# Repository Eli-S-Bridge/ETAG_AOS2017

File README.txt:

ETAG RFID reader Version1
(Distrubted at the American Ornithological Society Meeting, Lansing, MI, August 2017.

This repository contains:
  1) Eagle design files for the circuit board
  2) A board reference for using the Arduino app with the circuit board.
  3) Arduino code to install on the circuit board

SOFTWARE:

See the setup manual.

HARDWARE:

You can power the board from your USB port or use a 5V battery. 6V batteries seem to work OK too. We’ve tested 4AA batteries in series (which give ~6V). You can power the reader from the USB port or the push-in connectors. Check the + and - labels on the board before connecting the battery leads. The large switch on the circuit board alternates between power sources. If you have both USB and a battery connected, you will not really be able to turn the device off (but you can always use the reset button).

Antenna coils should have inductance of approximately 1.3 milliHenries. You can make the coils yourself by wrapping magnet wire around a form and measuring the inductance until you get it right. Don’t make them bigger than 15cm in diameter or they won’t work very well. You can also buy 1.25mH antennas that work pretty well here:

https://store.qkits.com/rfid/125khz-antenna-for-rfid-controllers-51-5mm.html

Tags need to work at 125kHz and follow the EM4100 communication protocol. Biomark tags generally follow the ISO11784/5 communication protocol will not work. Our favorite tag suppliers are www.cyntag.com (for PITtag style tags) and ibtechnology.co.uk (for RFID leg bands - look for “avian products”)

OTHER RESOURCES:

YouTube video demonstration: https://www.youtube.com/watch?v=-Nv7rSirzx8

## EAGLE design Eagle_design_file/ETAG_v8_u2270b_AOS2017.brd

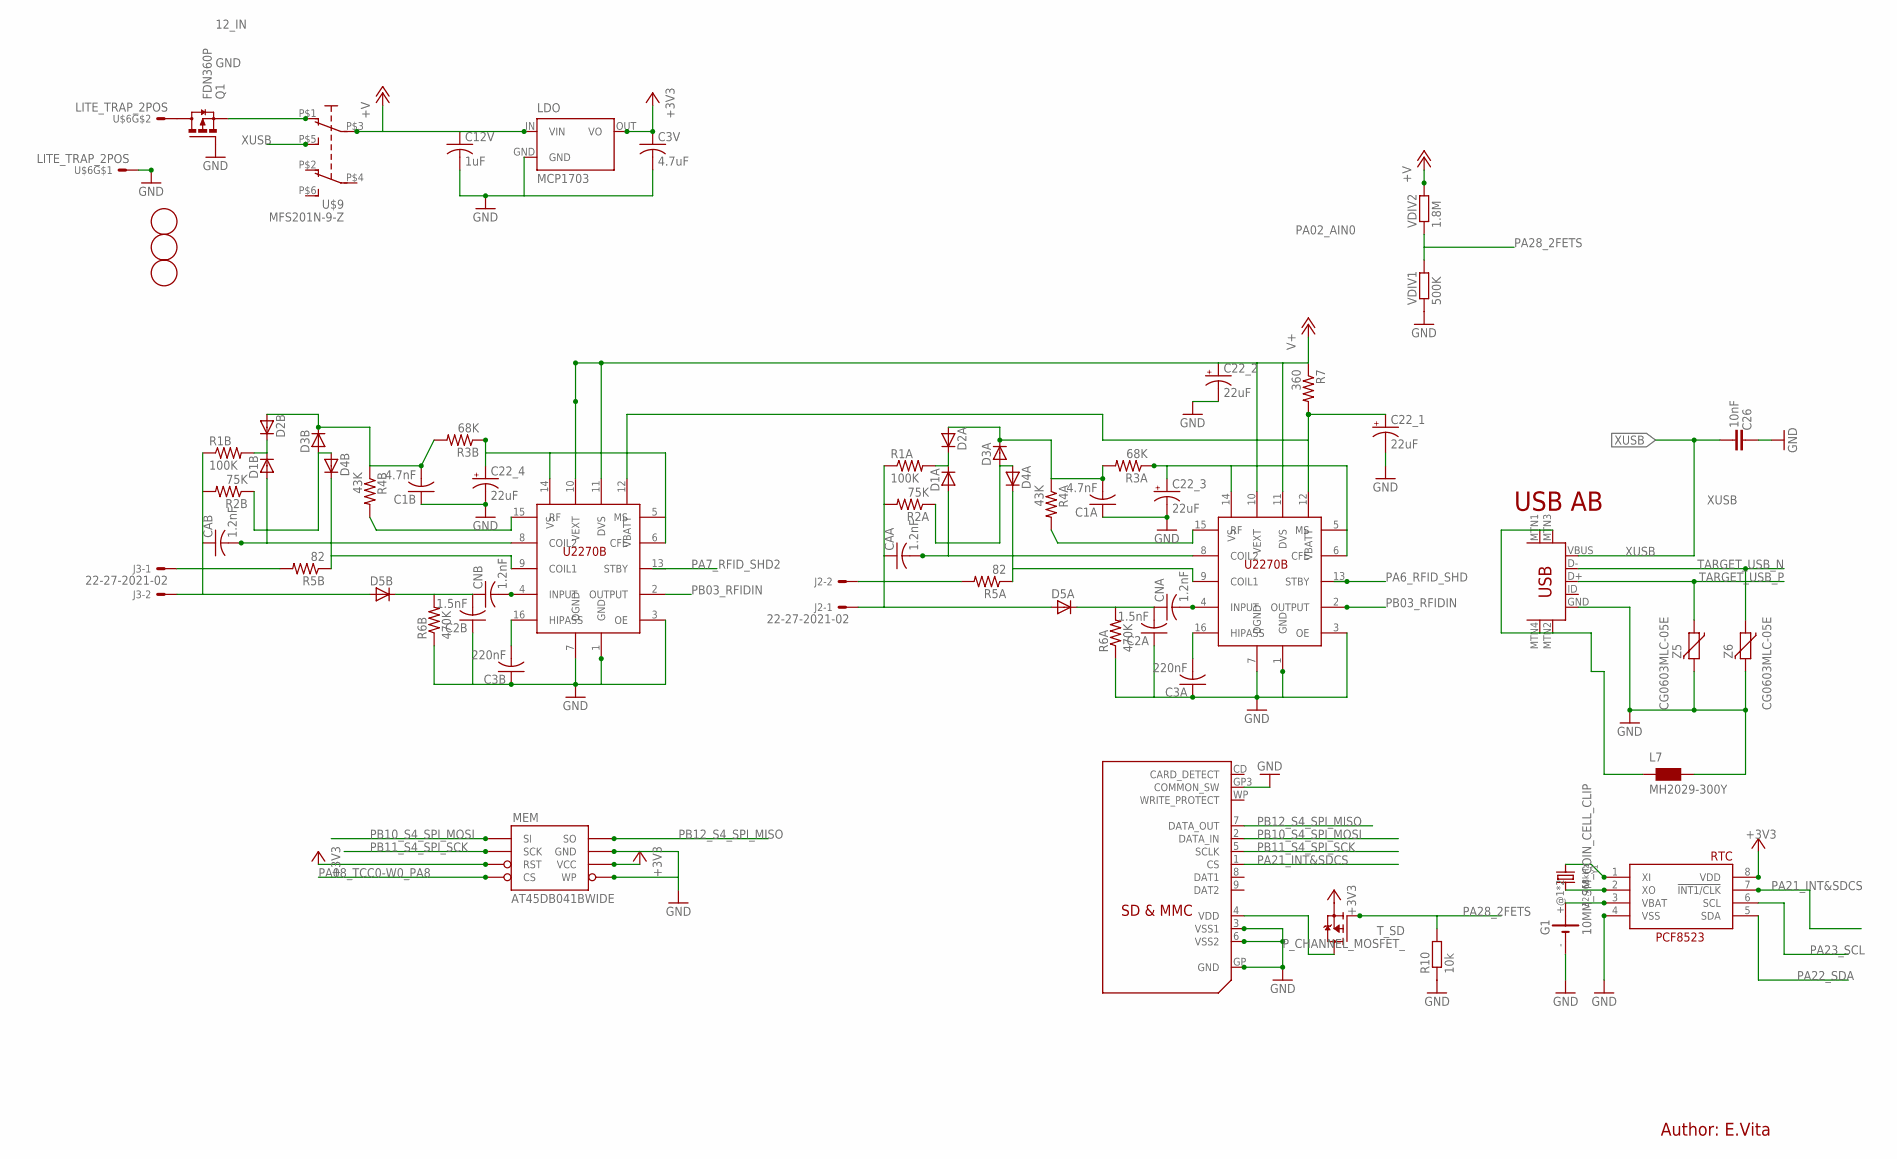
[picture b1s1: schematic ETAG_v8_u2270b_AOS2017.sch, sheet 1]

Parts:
C1A, C1B: 4.7nF; C0603-ROUND
C2A, C2B: 1.5nF; C0805
C3A, C3B: 220nF; C0603-ROUND
C3V: 4.7uF; C0805
C12V: 1uF; C0805
C22_1, C22_2, C22_3, C22_4: 22uF; 153CLV-0505
C26: 10nF; C0603-ROUND
CAA: 1.2nF; C0805
CAB: 1.2nF; C0805
CNA: 1.2nF; C0805
CNB: 1.2nF; C0805
D1A, D1B, D2A, D2B, D3A, D3B, D4A, D4B, D5A, D5B: D-GLASS_MELF; SOT-23_2PAD
FD1, FD2, FD3: FIDUCIALMOUNT; FIDUCIA-MOUNT
G1: 10MM_SM_COIN_CELL_CLIP
J2, J3: 22-27-2021-02; 6410-02
L7: MH2029-300Y; 0805
LDO: MCP1703; SOT89
MEM: AT45DB041BWIDE; SO08WIDE
Q1: FDN360P; SUPER-SOT3
R1A, R1B: 100K; C0603-ROUND
R2A, R2B: 75K; C0603-ROUND
R3A, R3B: 68K; C0603-ROUND
R4A, R4B: 43K; C0603-ROUND
R5A, R5B: 82; C0603-ROUND
R6A, R6B: 470K; C0603-ROUND
R7: 360; C0603-ROUND
R10: 10k; R0603-ROUND
RF_A: U2270B; SO16
RF_B: U2270B; SO16
RTC: RTC_PCF8523T; SOIC8_150MIL
T_SD: P_CHANNEL_MOSFET_; SOT23
U$4: SDMMC06132; 06132
U$6: LITE_TRAP_2POS; LITE_TRAP_MINI
U$9: MFS201N-9-Z
USB: USB-MINIB-5PIN; USB-MINIB
VDIV1: 500K; R0603-ROUND
VDIV2: 1.8M; R0603-ROUND
Y1: 32.768kHz; CRYSTAL_8X3.8
Z5, Z6: CG0603MLC-05E; CT/CN0603

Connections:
2GND: L7.1, USB.MTN1 (MTN2), USB.MTN2 (MTN3), USB.MTN3 (MTN1), USB.MTN4
12_IN: Q1.3 (D), U$6.P$3, U$6.P$4
+3V3: C3V.1, LDO.OUT (VO), MEM.3 (RST), MEM.6 (VCC), RTC.8 (VDD), T_SD.2 (S); also elsewhere on the board
GND: C1A.1, C1B.1, C2A.1, C2B.1, C3A.1, C3B.1, C3V.2, C12V.2, C22_1.-, C22_2.-, C22_3.-, C22_4.-, C26.2, G1.-, L7.2, LDO.GND, MEM.5 (WP), MEM.7 (GND), Q1.1 (G), R6A.1, R6B.1, R10.1, RF_A.1 (GND), RF_A.3 (OE), RF_A.7 (DGND), RF_B.1 (GND), RF_B.3 (OE), RF_B.7 (DGND), RTC.4 (VSS), U$4.3 (VSS1), U$4.6 (VSS2), U$4.GP (GND), U$4.GP3 (COMMON_SW), U$6.P$1, U$6.P$2, USB.GND, VDIV1.1, Z5.2, Z6.2; also elsewhere on the board
unnamed: RTC.2 (XO), Y1.P$4 (2)
unnamed: RTC.1 (XI), Y1.P$1 (1)
unnamed: C22_1.+, R7.2, RF_A.12 (VBATT), RF_B.12 (VBATT)
unnamed: C3A.2, RF_A.16 (HIPASS)
unnamed: CNA.2, RF_A.4 (INPUT)
unnamed: C2A.2, CNA.1, D5A.P$1 (C), R6A.2
unnamed: C1A.2, D2A.P$2 (A), D3A.P$1 (C), R3A.2, R4A.1
unnamed: J2.2, R5A.2
unnamed: J3.1, R5B.2
unnamed: Q1.2 (S), U$9.P$1 (O)
unnamed: D1A.P$1 (C), D2A.P$1 (C), R1A.2
unnamed: C3B.2, RF_B.16 (HIPASS)
unnamed: D3A.P$2 (A), D4A.P$2 (A), R2A.1
unnamed: CNB.2, RF_B.4 (INPUT)
unnamed: C2B.2, CNB.1, D5B.P$1 (C), R6B.2
unnamed: D4B.P$1 (C), R5B.1, RF_B.9 (COIL1)
unnamed: CAB.2, D1B.P$2 (A), RF_B.8 (COIL2)
unnamed: CAB.1, D5B.P$2 (A), J3.2, R1B.1, R2B.2
unnamed: R4B.2, RF_B.15 (RF)
unnamed: C22_4.+, R3B.1, RF_B.5 (MS), RF_B.6 (CFE), RF_B.14 (VS)
unnamed: D1B.P$1 (C), D2B.P$1 (C), R1B.2
unnamed: D3B.P$2 (A), D4B.P$2 (A), R2B.1
unnamed: C1B.2, D2B.P$2 (A), D3B.P$1 (C), R3B.2, R4B.1
unnamed: D4A.P$1 (C), R5A.1, RF_A.9 (COIL1)
unnamed: CAA.2, D1A.P$2 (A), RF_A.8 (COIL2)
unnamed: CAA.1, D5A.P$2 (A), J2.1, R1A.1, R2A.2
unnamed: R4A.2, RF_A.15 (RF)
unnamed: C22_3.+, R3A.1, RF_A.5 (MS), RF_A.6 (CFE), RF_A.14 (VS)
PA02_AIN0: VDIV1.2, VDIV2.1; also elsewhere on the board
PA6_RFID_SHD: RF_A.13 (STBY); also elsewhere on the board
PA7_RFID_SHD2: RF_B.13 (STBY); also elsewhere on the board
PA08_TCC0-W0_PA8: MEM.4 (CS); also elsewhere on the board
PA21_INT&SDCS: RTC.7 (!INT1/CLK), U$4.1 (CS); also elsewhere on the board
PA22_SDA: RTC.5 (SDA); also elsewhere on the board
PA23_SCL: RTC.6 (SCL); also elsewhere on the board
PA28_2FETS: R10.2, T_SD.1 (G); also elsewhere on the board
PB03_RFIDIN: RF_A.2 (OUTPUT), RF_B.2 (OUTPUT); also elsewhere on the board
PB10_S4_SPI_MOSI: MEM.1 (SI), U$4.2 (DATA_IN); also elsewhere on the board
PB11_S4_SPI_SCK: MEM.2 (SCK), U$4.5 (SCLK); also elsewhere on the board
PB12_S4_SPI_MISO: MEM.8 (SO), U$4.7 (DATA_OUT); also elsewhere on the board
TARGET_USB_N: USB.D-, Z6.1; also elsewhere on the board
TARGET_USB_P: USB.D+, Z5.1; also elsewhere on the board
VBAT1: G1.+@1 (+), G1.+@2 (+), RTC.3 (VBAT)
VDD: T_SD.3 (D), U$4.4 (VDD)
V_IN: C12V.1, C22_2.+, LDO.IN (VIN), R7.1, RF_A.10 (VEXT), RF_A.11 (DVS), RF_B.10 (VEXT), RF_B.11 (DVS), U$9.P$3, VDIV2.2; also elsewhere on the board
XUSB: C26.1, U$9.P$5 (S), USB.VBUS

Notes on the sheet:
USB AB
Author: E.Vita

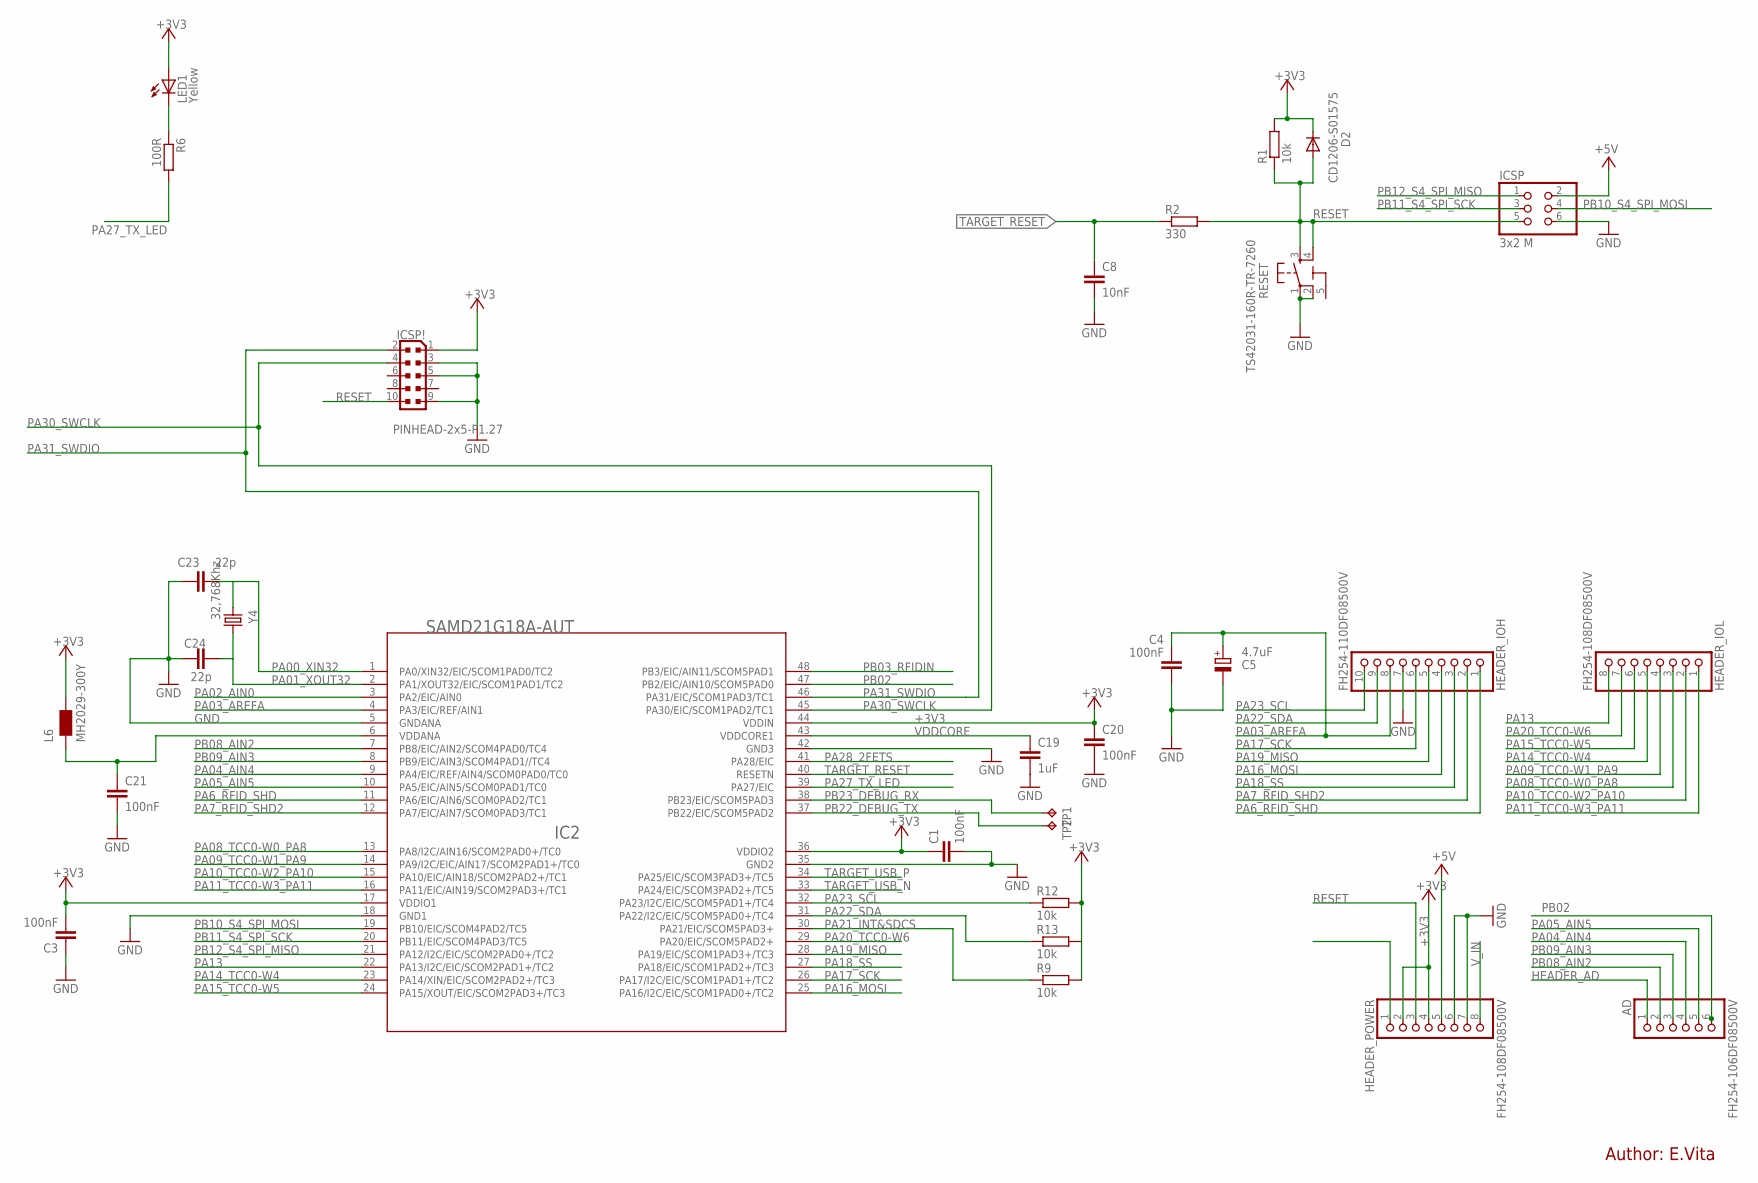
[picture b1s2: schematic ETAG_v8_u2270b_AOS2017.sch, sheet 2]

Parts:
AD: FH254-106DF08500V; 1X06
C1, C3, C4, C20, C21: 100nF; C0603-ROUND
C5: 4.7uF; SMC_A
C8: 10nF; C0603-ROUND
C19: 1uF; C0603-ROUND
C23, C24: 22p; C0603-ROUND
D2: CD1206-S01575; MINIMELF
HEADER_IOH: FH254-110DF08500V; 1X10
HEADER_IOL: FH254-108DF08500V; 1X08
HEADER_POWER: FH254-108DF08500V; 1X08
IC2: SAMD21G18A-AUT; TQFP48-7X7
ICSP: 3x2 M; 2X03
ICSP!: PINHEAD-2x5-P1.27; PINHEAD_2X05_127
L6: MH2029-300Y; 0805
LED1: Yellow; CHIPLED_0805
R1, R9, R12, R13: 10k; R0603-ROUND
R2: 330; R0603-ROUND
R6: 100R; R0603-ROUND
RESET: TS42031-160R-TR-7260; TS42
TP1, TP2: TPTP15R; TP15R
Y4: 32,768Khz; RESONATOR_EPSON_FC_145

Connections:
5-GND: RESET.5 (5-GND)
+3V3: C1.1, C3.2, C20.1, D2.C, HEADER_POWER.2, HEADER_POWER.4, IC2.17 (VDDIO1), IC2.36 (VDDIO2), IC2.44 (VDDIN), ICSP!.1, L6.2, LED1.A, R1.2, R9.2, R12.2, R13.2; also elsewhere on the board
+5V: HEADER_POWER.5, ICSP.2
GND: C1.2, C3.1, C4.2, C5.-, C8.2, C19.2, C20.2, C21.2, C23.1, C24.1, HEADER_IOH.7, HEADER_POWER.6, HEADER_POWER.7, IC2.5 (GNDANA), IC2.18 (GND1), IC2.35 (GND2), IC2.42 (GND3), ICSP.6, ICSP!.3, ICSP!.5, ICSP!.9, RESET.1, RESET.2; also elsewhere on the board
HEADER_AD: AD.1
unnamed: LED1.C, R6.1
unnamed: C21.1, IC2.6 (VDDANA), L6.1
PA00_XIN32: C23.2, IC2.1 (PA0/XIN32/EIC/SCOM1PAD0/TC2), Y4.P$1 (1)
PA01_XOUT32: C24.2, IC2.2 (PA1/XOUT32/EIC/SCOM1PAD1/TC2), Y4.P$2 (2)
PA02_AIN0: IC2.3 (PA2/EIC/AIN0); also elsewhere on the board
PA03_AREFA: C4.1, C5.+, HEADER_IOH.8, IC2.4 (PA3/EIC/REF/AIN1)
PA04_AIN4: AD.4, IC2.9 (PA4/EIC/REF/AIN4/SCOM0PAD0/TC0)
PA05_AIN5: AD.5, IC2.10 (PA5/EIC/AIN5/SCOM0PAD1/TC0)
PA6_RFID_SHD: HEADER_IOH.1, IC2.11 (PA6/EIC/AIN6/SCOM0PAD2/TC1); also elsewhere on the board
PA7_RFID_SHD2: HEADER_IOH.2, IC2.12 (PA7/EIC/AIN7/SCOM0PAD3/TC1); also elsewhere on the board
PA08_TCC0-W0_PA8: HEADER_IOL.3, IC2.13 (PA8/I2C/AIN16/SCOM2PAD0+/TC0); also elsewhere on the board
PA09_TCC0-W1_PA9: HEADER_IOL.4, IC2.14 (PA9/I2C/EIC/AIN17/SCOM2PAD1+/TC0)
PA10_TCC0-W2_PA10: HEADER_IOL.2, IC2.15 (PA10/EIC/AIN18/SCOM2PAD2+/TC1)
PA11_TCC0-W3_PA11: HEADER_IOL.1, IC2.16 (PA11/EIC/AIN19/SCOM2PAD3+/TC1)
PA13: HEADER_IOL.8, IC2.22 (PA13/I2C/EIC/SCOM2PAD1+/TC2)
PA14_TCC0-W4: HEADER_IOL.5, IC2.23 (PA14/XIN/EIC/SCOM2PAD2+/TC3)
PA15_TCC0-W5: HEADER_IOL.6, IC2.24 (PA15/XOUT/EIC/SCOM2PAD3+/TC3)
PA16_MOSI: HEADER_IOH.4, IC2.25 (PA16/I2C/EIC/SCOM1PAD0+/TC2)
PA17_SCK: HEADER_IOH.6, IC2.26 (PA17/I2C/EIC/SCOM1PAD1+/TC2)
PA18_SS: HEADER_IOH.3, IC2.27 (PA18/EIC/SCOM1PAD2+/TC3)
PA19_MISO: HEADER_IOH.5, IC2.28 (PA19/EIC/SCOM1PAD3+/TC3)
PA20_TCC0-W6: HEADER_IOL.7, IC2.29 (PA20/EIC/SCOM5PAD2+)
PA21_INT&SDCS: IC2.30 (PA21/EIC/SCOM5PAD3+), R9.1; also elsewhere on the board
PA22_SDA: HEADER_IOH.9, IC2.31 (PA22/I2C/EIC/SCOM5PAD0+/TC4), R13.1; also elsewhere on the board
PA23_SCL: HEADER_IOH.10, IC2.32 (PA23/I2C/EIC/SCOM5PAD1+/TC4), R12.1; also elsewhere on the board
PA27_TX_LED: IC2.39 (PA27/EIC), R6.2
PA28_2FETS: IC2.41 (PA28/EIC); also elsewhere on the board
PA30_SWCLK: IC2.45 (PA30/EIC/SCOM1PAD2/TC1), ICSP!.4
PA31_SWDIO: IC2.46 (PA31/EIC/SCOM1PAD3/TC1), ICSP!.2
PB02: AD.6, IC2.47 (PB2/EIC/AIN10/SCOM5PAD0)
PB03_RFIDIN: IC2.48 (PB3/EIC/AIN11/SCOM5PAD1); also elsewhere on the board
PB08_AIN2: AD.2, IC2.7 (PB8/EIC/AIN2/SCOM4PAD0/TC4)
PB09_AIN3: AD.3, IC2.8 (PB9/EIC/AIN3/SCOM4PAD1//TC4)
PB10_S4_SPI_MOSI: IC2.19 (PB10/EIC/SCOM4PAD2/TC5), ICSP.4; also elsewhere on the board
PB11_S4_SPI_SCK: IC2.20 (PB11/EIC/SCOM4PAD3/TC5), ICSP.3; also elsewhere on the board
PB12_S4_SPI_MISO: IC2.21 (PA12/I2C/EIC/SCOM2PAD0+/TC2), ICSP.1; also elsewhere on the board
PB22_DEBUG_TX: IC2.37 (PB22/EIC/SCOM5PAD2), TP2.TP
PB23_DEBUG_RX: IC2.38 (PB23/EIC/SCOM5PAD3), TP1.TP
RESET: D2.A, HEADER_POWER.3, ICSP.5, ICSP!.10, R1.1, R2.2, RESET.3, RESET.4
TARGET_RESET: C8.1, IC2.40 (RESETN), R2.1
TARGET_USB_N: IC2.33 (PA24/EIC/SCOM3PAD2+/TC5); also elsewhere on the board
TARGET_USB_P: IC2.34 (PA25/EIC/SCOM3PAD3+/TC5); also elsewhere on the board
VDDCORE: C19.1, IC2.43 (VDDCORE1)
V_IN: HEADER_POWER.8; also elsewhere on the board

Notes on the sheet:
Author: E.Vita

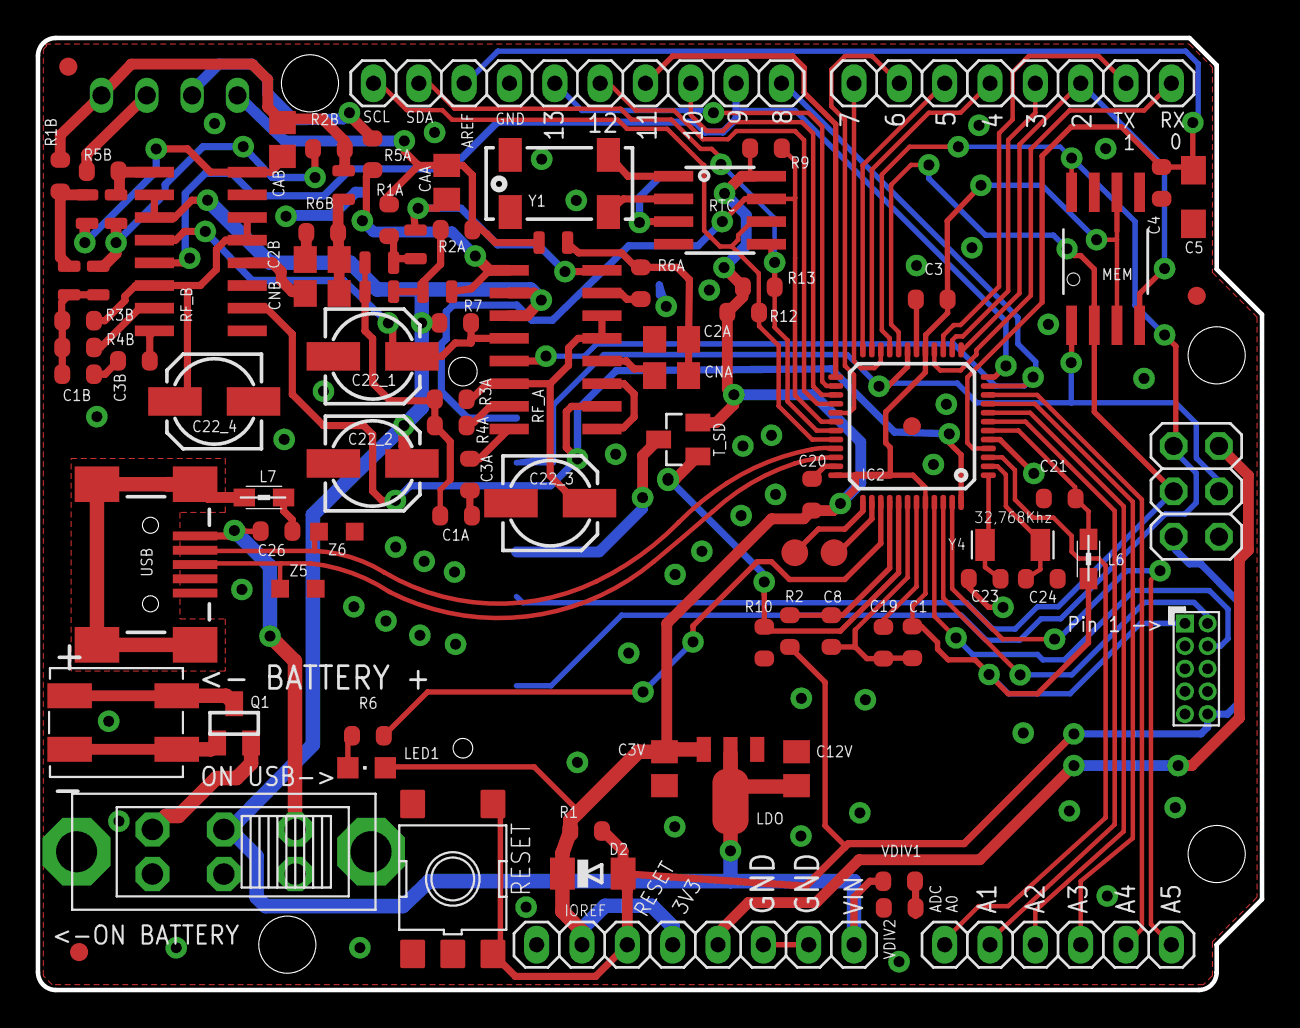
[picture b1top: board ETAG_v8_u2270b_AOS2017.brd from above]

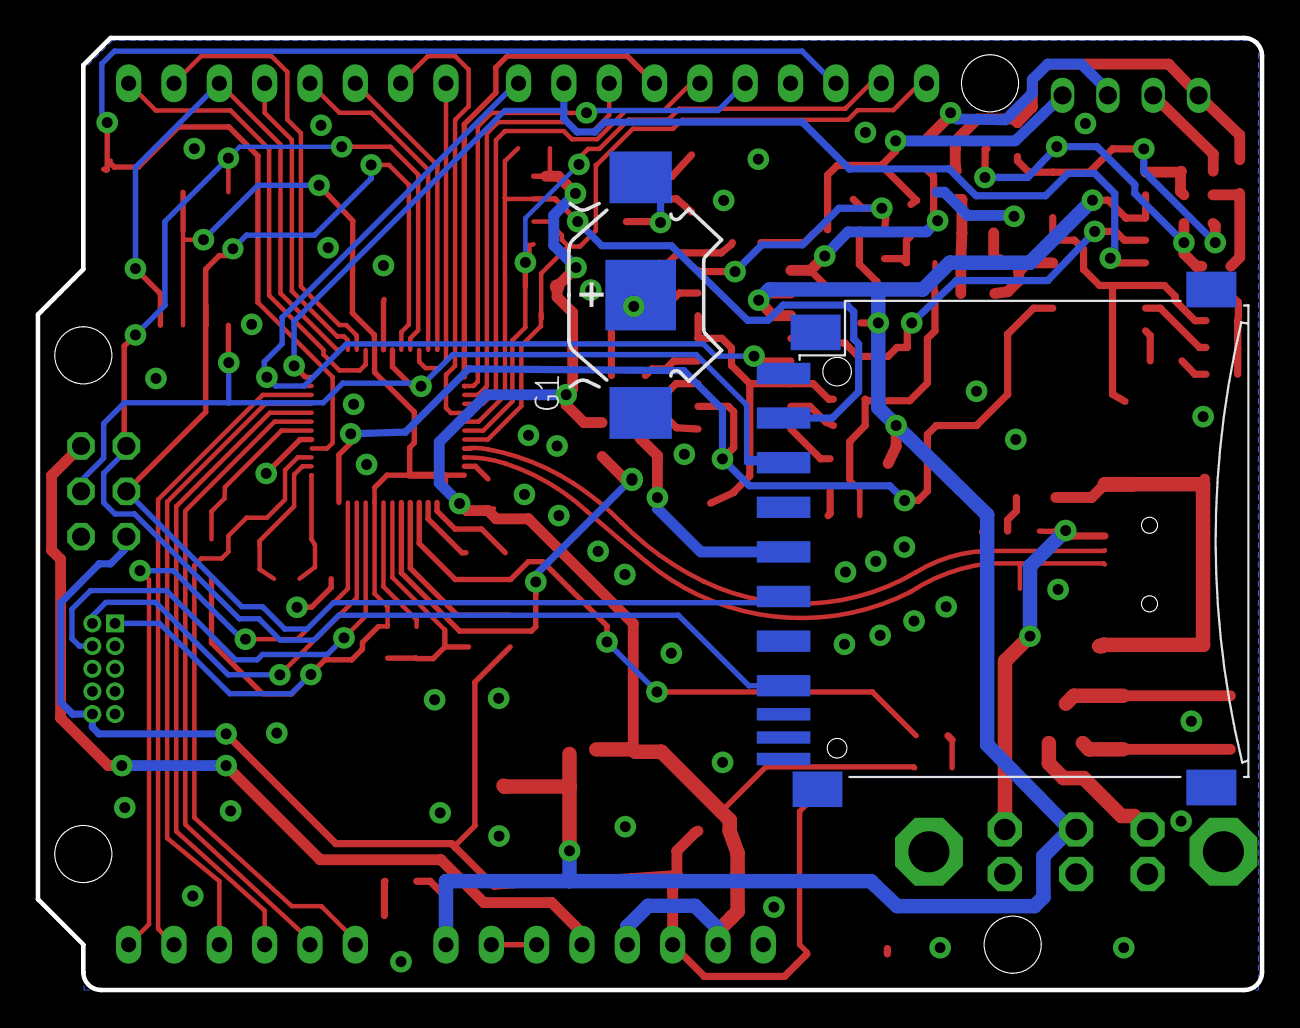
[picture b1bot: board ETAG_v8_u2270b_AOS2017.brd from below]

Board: 4 copper layers, 68.6 x 53.3 mm, 94 parts (2 on the bottom side), 80 nets.

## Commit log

2017-07-31 Initial commit
    Eagle files and Arduino script for ETAG readers distributed at AOS2017
2017-07-31 Added README and board ref
2017-07-31 edits to readme
2017-07-31 added to README and added more code annotation
2017-07-31 fixed gitignore
2017-07-31 removed DS_Store
2017-08-02 Added setup manual
2017-08-02 updated with ref to setup manual

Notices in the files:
parts and their libraries:
SparkFun-DigitalIC: Licensing: Creative Commons ShareAlike 4.0 International - https://creativecommons.org/licenses/by-sa/4.0
